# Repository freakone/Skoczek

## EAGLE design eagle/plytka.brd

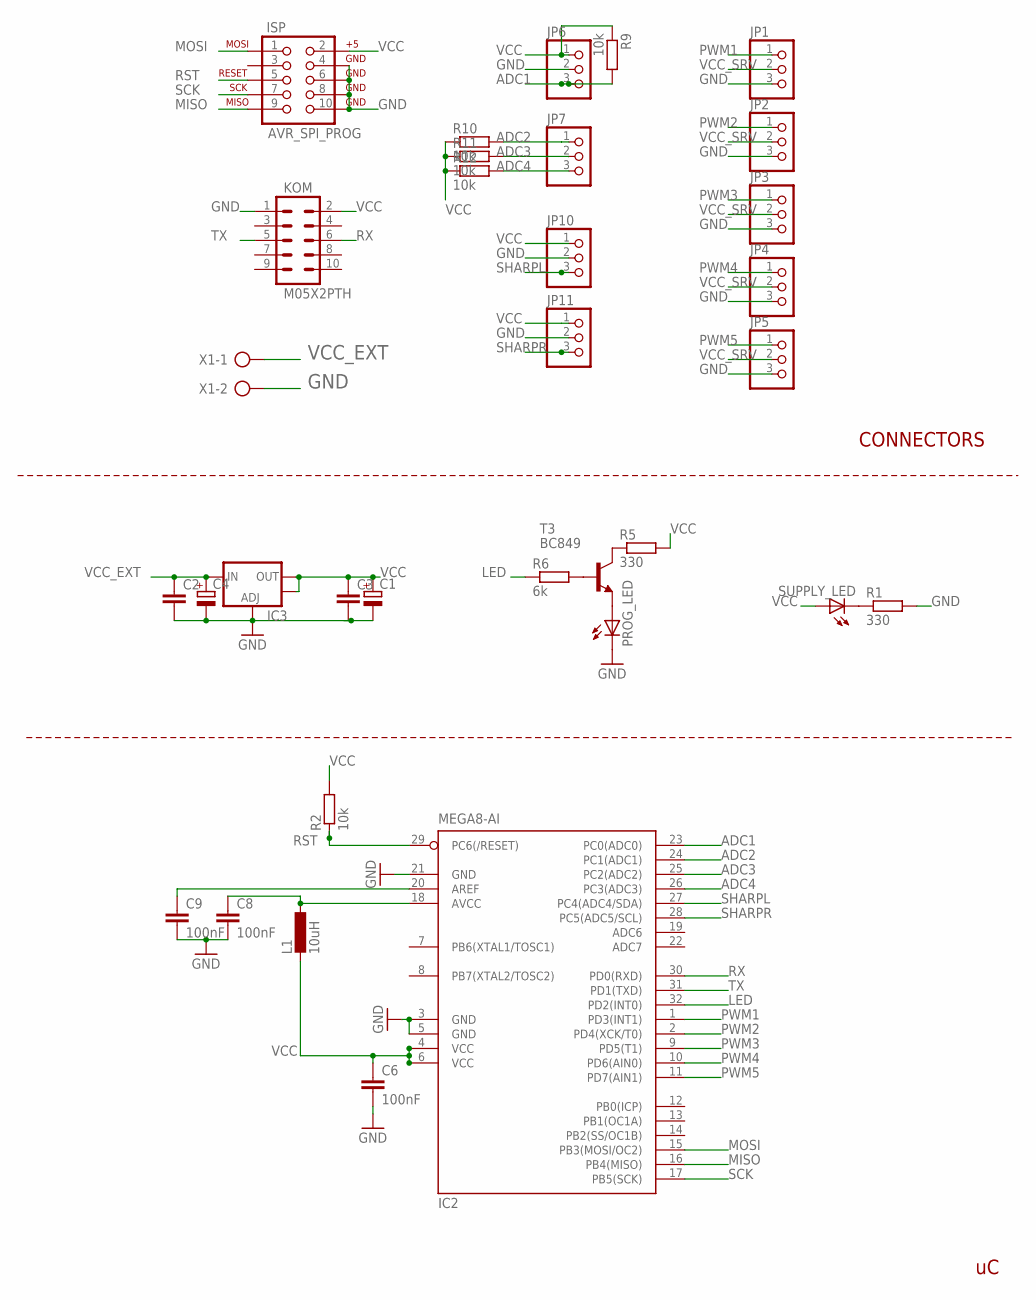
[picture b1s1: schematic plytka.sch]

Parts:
C1, C4: CPOL-EUE5-10.5; E5-10,5
C2, C3: C-EUC0805; C0805
C6, C8, C9: 100nF; C0805
IC2: MEGA8-AI; TQFP32-08
IC3: V_REG_LM1117SOT223; SOT223
ISP: AVR_SPI_PROG; AVR_ICSP
JP1, JP2, JP3, JP4, JP5, JP6, JP7, JP10, JP11: PINHD-1X3; 1X03
KOM: M05X2PTH; AVR_ICSP
L1: 10uH; L2012C
PROG_LED: LEDCHIPLED_0805; CHIPLED_0805
R1, R5: 330; R0805
R2, R9, R10, R11, R12: 10k; M0805
R6: 6k; R0805
SUPPLY_LED: LEDCHIPLED_0805; CHIPLED_0805
T3: BC849; SOT23
X1: AK300/2

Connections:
ADC1: IC2.23 (PC0(ADC0)), JP6.3, R9.2
ADC2: IC2.24 (PC1(ADC1)), JP7.1, R10.2
ADC3: IC2.25 (PC2(ADC2)), JP7.2, R11.2
ADC4: IC2.26 (PC3(ADC3)), JP7.3, R12.2
GND: C1.-, C2.2, C3.2, C4.-, C6.2, C8.2, C9.2, IC2.3 (GND), IC2.5 (GND), IC2.21 (GND), IC3.1 (ADJ), ISP.4, ISP.6, ISP.8, ISP.10, JP1.3, JP2.3, JP3.3, JP4.3, JP5.3, JP6.2, JP10.2, JP11.2, KOM.1, PROG_LED.C, R1.2, X1.2
LED: IC2.32 (PD2(INT0)), R6.1
MISO: IC2.16 (PB4(MISO)), ISP.9
MOSI: IC2.15 (PB3(MOSI/OC2)), ISP.1
unnamed: R1.1, SUPPLY_LED.C
unnamed: C9.1, IC2.20 (AREF)
unnamed: PROG_LED.A, T3.2 (E)
unnamed: R6.2, T3.1 (B)
unnamed: R5.1, T3.3 (C)
unnamed: C8.1, IC2.18 (AVCC), L1.1
PWM1: IC2.1 (PD3(INT1)), JP1.1
PWM2: IC2.2 (PD4(XCK/T0)), JP2.1
PWM3: IC2.9 (PD5(T1)), JP3.1
PWM4: IC2.10 (PD6(AIN0)), JP4.1
PWM5: IC2.11 (PD7(AIN1)), JP5.1
RST: IC2.29 (PC6(/RESET)), ISP.5, R2.1
RX: IC2.30 (PD0(RXD)), KOM.6
SCK: IC2.17 (PB5(SCK)), ISP.7
SHARPL: IC2.27 (PC4(ADC4/SDA)), JP10.3
SHARPR: IC2.28 (PC5(ADC5/SCL)), JP11.3
TX: IC2.31 (PD1(TXD)), KOM.5
VCC: C1.+, C3.1, C6.1, IC2.4 (VCC), IC2.6 (VCC), IC3.2 (OUT), IC3.4 (OUT), ISP.2, JP6.1, JP10.1, JP11.1, KOM.2, L1.2, R2.2, R5.2, R9.1, R10.1, R11.1, R12.1, SUPPLY_LED.A
VCC_EXT: C2.1, C4.+, IC3.3 (IN), X1.1
VCC_SRV: JP1.2, JP2.2, JP3.2, JP4.2, JP5.2

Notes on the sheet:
CONNECTORS

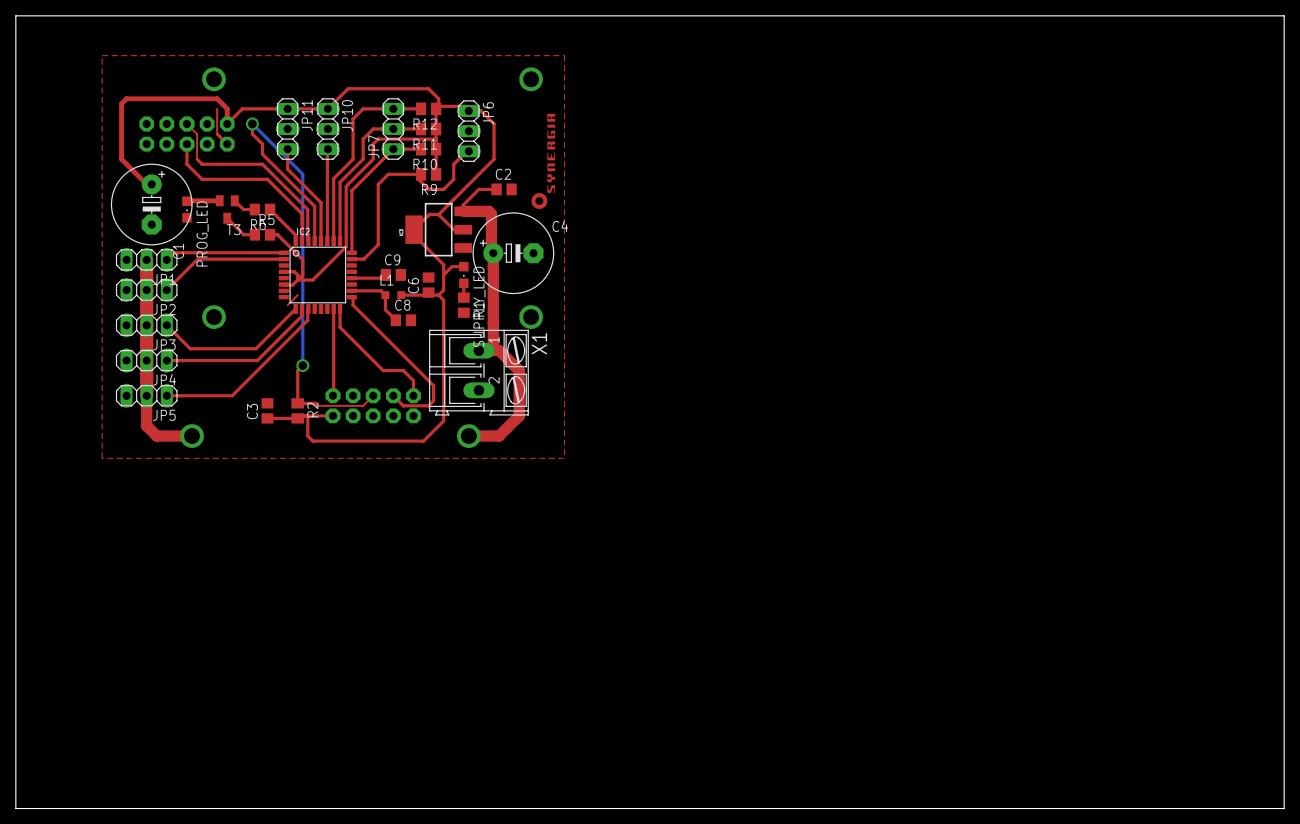
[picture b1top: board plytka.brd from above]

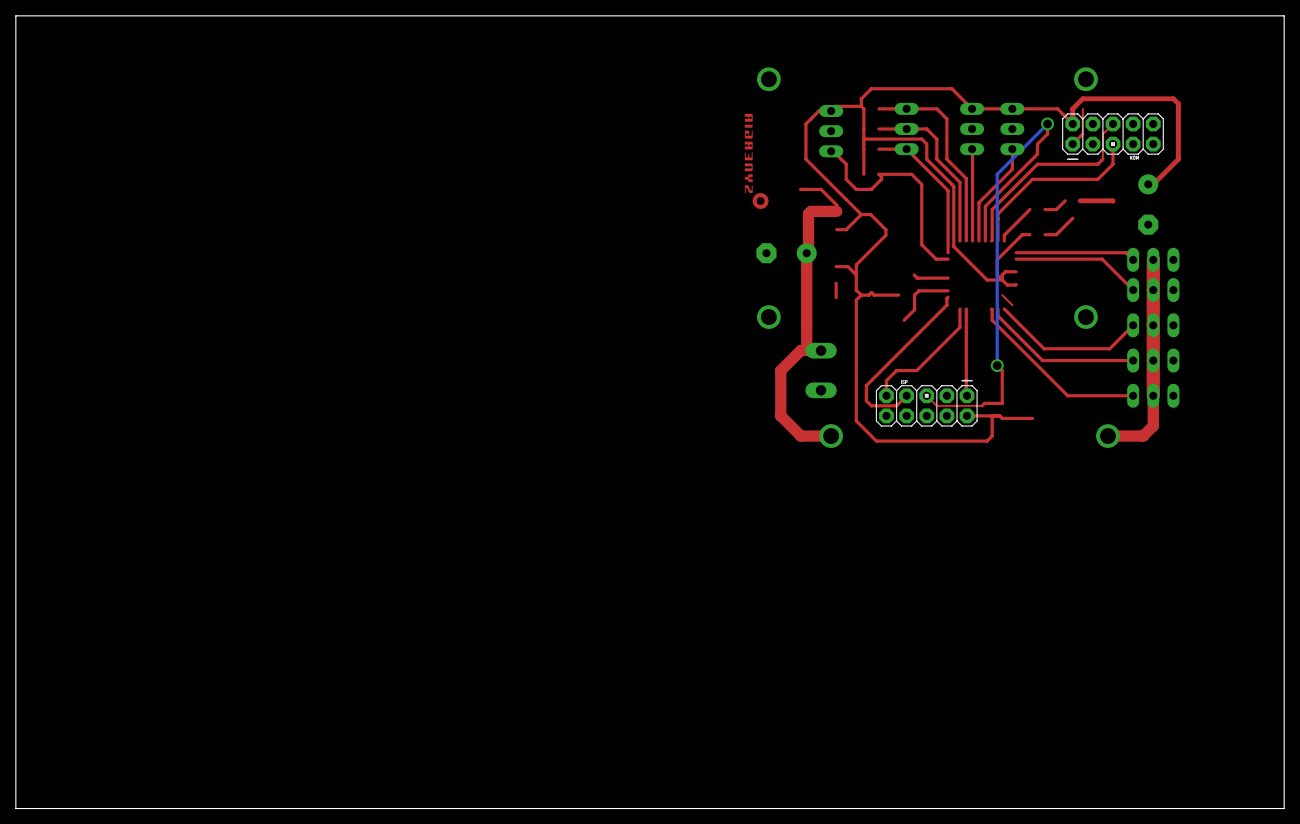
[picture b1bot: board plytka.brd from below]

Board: 2 copper layers, 160.0 x 100.0 mm, 34 parts (2 on the bottom side), 28 nets.

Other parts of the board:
U$1: SYNERGIA_12MM

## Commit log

2013-12-16 first push
2014-01-01 working!
2014-01-02 poprawki
2014-01-02 pimp wyrównywania
2014-01-02 corner case
2014-01-03 porządek

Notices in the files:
parts and their libraries:
SparkFun-Connectors: Licensing: CC v3.0 Share-Alike You are welcome to use this library for commercial purposes.
